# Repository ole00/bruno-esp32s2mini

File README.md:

# bruno ESP32-S2-Mini 
Break-out board for ESP32-S2-Mini to Arduino UNO style base board.

This PCB allows you to experiment with various Arduino 3.3V compatible shields while using a cheap
and powerful ESP32-S2-Mini board. 

This board can only handle IO voltages up to 3.3V, therefore not every Arduino shield is compatible.

**The features are as follows:**
- ESP32-S2-Mini has more memory, more flash and faster CPU speed compared to Arduino UNO
- no additional components (except the optional LED on GPIO 39)
- simple to assemble (just solder the Mini board and Arduino GPIO headers).
- Digital IO numbering mostly follows AVR UNO pin nmubers
- Extra GPIO pins exposed on the 6-pin side header
- USB-C powered

**Differences comapred to Arduino UNO**
- 3.3V IO logic only!
- IOREF pin hardwired to 3.3V
- no external AREF, use the internal Analog reference of ESP32-S2
- only 5 Analog pins on the Analog header (A5 is digital only)
- extra analog pins on Digital header pins 1 - 13 (ADC1_0 - ADC2_2)
- no TTL Uart on digital pins 0 and 1 (however the serial input/output is mapped
  to the USB port)
- The reset pin on Arduino board is not connected to the ESP32-S2-Mini. There is a convenient
  pad placed next to the S2-Mini reset button, so if you need the external reset functionality
  you can wire the S2-Mini reset button and the reset pad.
- The S2-Mini has an onboard LED (located between the USB connector and the '0' button) that is
  connected to GPIO 15 (Arduino UNO A1 pin). That might cause issues with some designs. In such
  case remove the LED or the current limiting resistor on the S2-Mini board to fix the issue
  (the LED will stop working obviously).
- Note that the 3.3V rail is powered by a small onboard LDO (voltage regulator) which also
  powers the MCU. If you need to use higher number of peripherals on the 3.3V power rail then
  consider adding another LDO (supplied by the 5V rail) to your design/shield. Generally speaking,
  for few LEDS and a couple of extra ICS (like accelerometer, sensors etc.) the LDO is OK and you'll
  not need to add an extra LDO.
- WiFi functionality is untested. It might work, but the PCB antenna is close to the base board
  so the transmit/reception will not be great. If you'll use a shield that covers the antenna
  the maximum connection distance will be even shorter.

 **Arduino IDE setup**
 
 Install the ESP32 platfrom from Espressif in boards manager. Then select the Board as 'ESP32S2 Dev Module'.
 The rest of the board configuration options is as follows:

- Ensure "USB CDC On Boot" is Enabled, so that you have the Serial port mapped to USB.
- The sketch upload works automatically, no need to press reset or boot buttons (tested with IDE 2.2.1).
- Note that my CPU frequency is lowered to 40MHz. This might improve compatibility with UNO sketches when they use
  bit-banging technique.

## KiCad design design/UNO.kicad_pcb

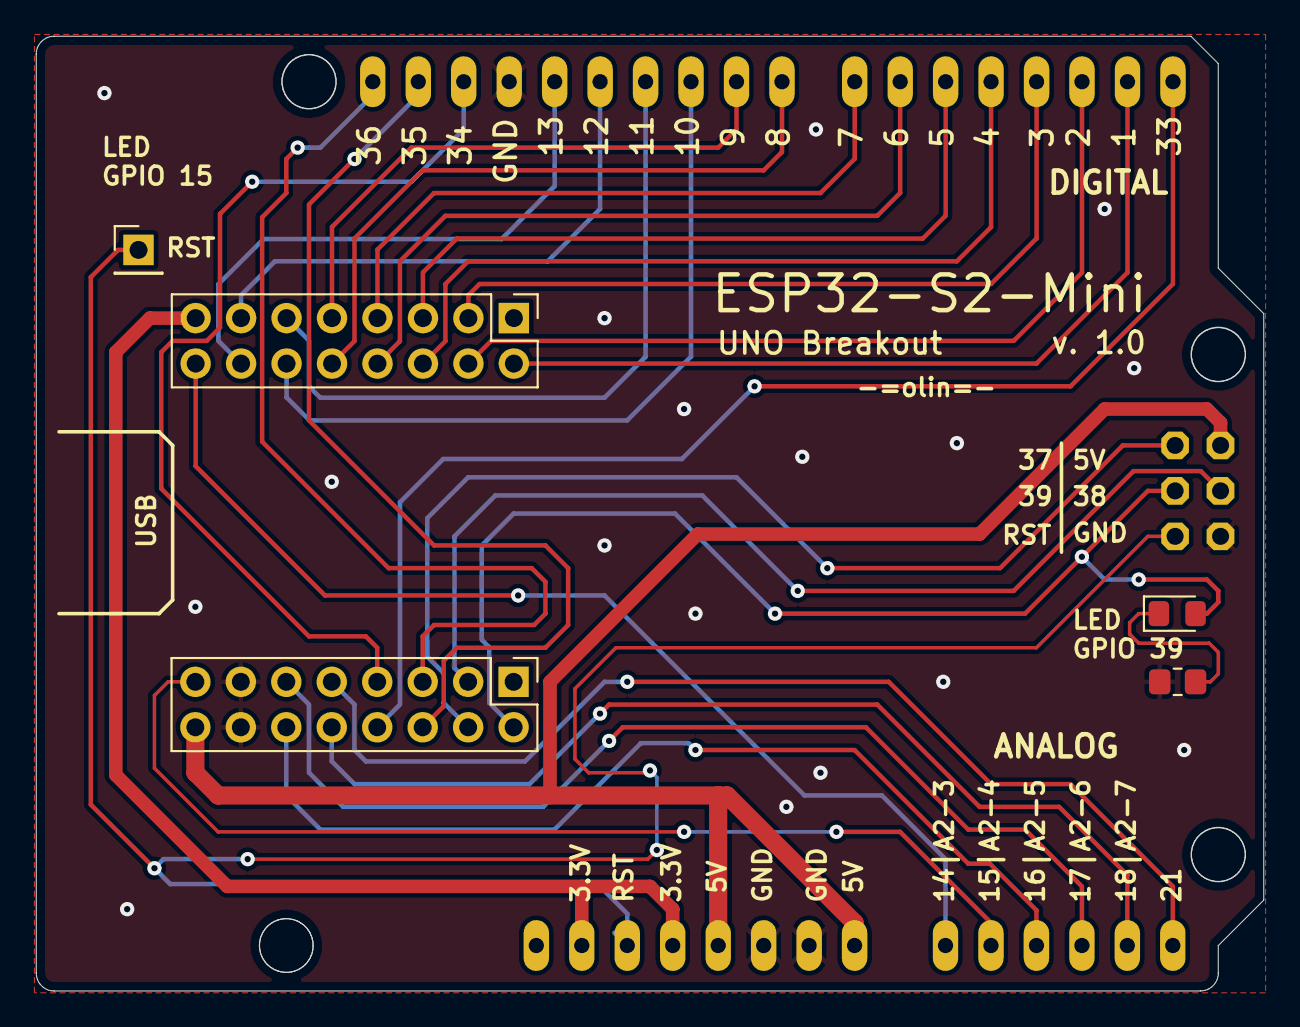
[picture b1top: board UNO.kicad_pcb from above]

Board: 2 copper layers, 68.6 x 53.3 mm, 4 parts (0 on the bottom side), 4 nets.

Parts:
ANALOG: -; 1X14_
DIGITAL: -; 1X18_
RST: PinHeader_1x01_P2.54mm_Vertical
SPI1: -; 2X03

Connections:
+3V3: ANALOG.2, ANALOG.4
+5V: ANALOG.5, ANALOG.8, SPI1.2
GND: ANALOG.6, ANALOG.7, DIGITAL.15, SPI1.6
TRG_RST: ANALOG.3, RST.1, SPI1.5

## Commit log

2024-04-20 added KiCAD design files
2024-04-20 added gerbers
2024-04-20 added images
2024-04-20 Update README.md - reset pin
2024-04-20 Update README.md - onboard LED
2024-04-20 Update README.md - power and WiFi
